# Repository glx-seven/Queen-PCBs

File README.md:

# Queen-PCBs
These are some Blinky-LED pendants I made a while ago. 

The main components are:
* BQ25570 energy harvesting controller
* KXOB25-05X3F mini solar cell
* MAL219691153E3 4F super-cap (probably has to be replaced with something else due to availability)
* PIC16LF18346-E/GZ (QFN20) MCU (if you're using 1.8V turn off the brown-out detection to make it run properly)

The programming pins match the PICKIT debugger, so you can stick some pogo-pins in the connector and hold it onto the pins to flash th firmware.
I did also upload the MPLAB-X project files for the firmware, it's not very good or complex tho, it just blinks some LEDs.

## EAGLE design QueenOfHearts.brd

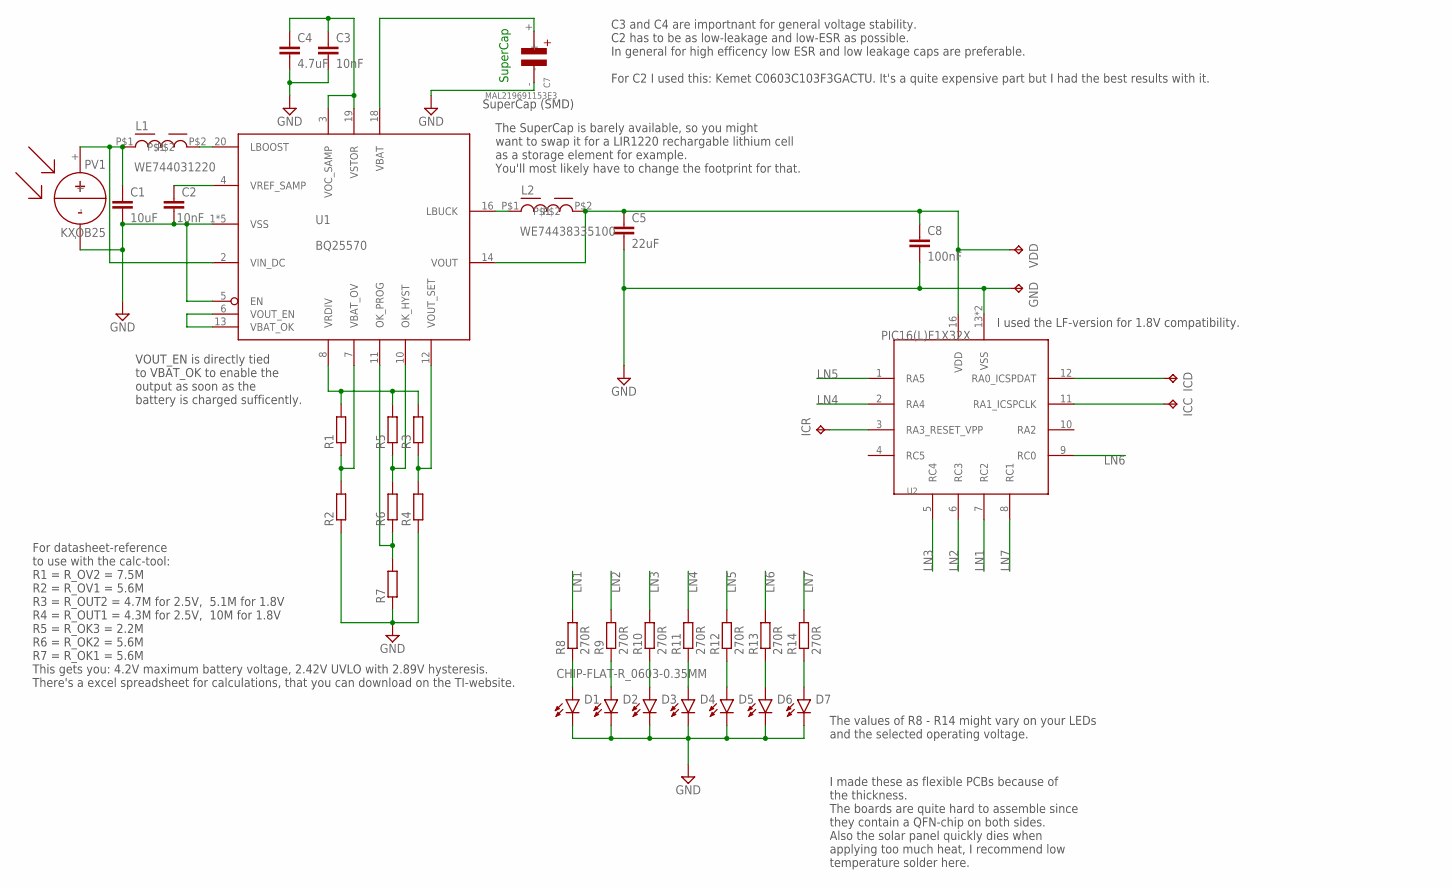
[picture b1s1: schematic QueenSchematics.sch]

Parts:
C1: 10uF; C0603K
C2, C3: 10nF; C0603K
C4: 4.7uF; C0603K
C5: 22uF; C0603K
C7: MAL219691153E3; MAL219691153E2
C8: 100nF; C0603K
D1, D2, D3, D4, D5, D6, D7: CHIP-FLAT-R_0603-0.35MM; LEDC1608X35N
GND: TPTP06SQ; TP06SQ
ICC: TPTP06SQ; TP06SQ
ICD: TPTP06SQ; TP06SQ
ICR: TPTP06SQ; TP06SQ
L1: WE744031220
L2: WE74438335100
PV1: KXOB25
R1, R2, R3, R4, R5, R6, R7: R-EU_R0603; R0603
R8, R9, R10, R11, R12, R13, R14: 270R; R0603
U1: BQ25570; QFN50P350X350X90-21T205N
U2: PIC16(L)F1X32X; QFN65P400X400X50-17T260N
VDD: TPTP06SQ; TP06SQ

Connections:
GND: C1.2, C2.2, C3.2, C4.2, C5.2, C7.-, C8.2, D1.C, D2.C, D3.C, D4.C, D5.C, D6.C, D7.C, GND.TP, PV1.-, R2.1, R4.1, R7.1, U1.1 (VSS), U1.5 (EN), U1.9 (VSS), U1.15 (VSS), U1.17 (VSS), U1.21 (VSS), U2.13 (VSS), U2.17 (VSS)
LN1: R8.2, U2.7 (RC2)
LN2: R9.2, U2.6 (RC3)
LN3: R10.2, U2.5 (RC4)
LN4: R11.2, U2.2 (RA4)
LN5: R12.2, U2.1 (RA5)
LN6: R13.2, U2.9 (RC0)
LN7: R14.2, U2.8 (RC1)
unnamed: L1.P$2, U1.20 (LBOOST)
unnamed: C1.1, L1.P$1, PV1.+, U1.2 (VIN_DC)
unnamed: C2.1, U1.4 (VREF_SAMP)
unnamed: L2.P$1, U1.16 (LBUCK)
unnamed: C3.1, C4.1, U1.3 (VOC_SAMP), U1.19 (VSTOR)
unnamed: U1.6 (VOUT_EN), U1.13 (VBAT_OK)
unnamed: C5.1, C8.1, L2.P$2, U1.14 (VOUT), U2.16 (VDD), VDD.TP
unnamed: C7.+, U1.18 (VBAT)
unnamed: R1.1, R2.2, U1.7 (VBAT_OV)
unnamed: R5.1, R6.2, U1.10 (OK_HYST)
unnamed: R3.1, R4.2, U1.12 (VOUT_SET)
unnamed: R6.1, R7.2, U1.11 (OK_PROG)
unnamed: ICR.TP, U2.3 (RA3_RESET_VPP)
unnamed: ICD.TP, U2.12 (RA0_ICSPDAT)
unnamed: ICC.TP, U2.11 (RA1_ICSPCLK)
unnamed: D1.A, R8.1
unnamed: D2.A, R9.1
unnamed: D3.A, R10.1
unnamed: D4.A, R11.1
unnamed: D5.A, R12.1
unnamed: D6.A, R13.1
unnamed: D7.A, R14.1
VRDRV: R1.2, R3.2, R5.2, U1.8 (VRDIV)

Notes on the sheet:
For datasheet-reference to use with the calc-tool: R1 = R_OV2 = 7.5M R2 = R_OV1 = 5.6M R3 = R_OUT2 = 4.7M for 2.5V, 5.1M for 1.8V R4 = R_OUT1 = 4.3M for 2.5V, 10M for 1.8V R5 = R_OK3 = 2.2M R6 = R_OK2 = 5.6M R7 = R_OK1 = 5.6M This gets you: 4.2V maximum battery voltage, 2.42V UVLO with 2.89V hyster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
SuperCap
SuperCap (SMD)
C3 and C4 are importnant for general voltage stability. C2 has to be as low-leakage and low-ESR as possible. In general for high efficency low ESR and low leakage caps are preferable. For C2 I used this: Kemet C0603C103F3GACTU. It's a quite expensive part but I had the best results with it.
VOUT_EN is directly tied to VBAT_OK to enable the output as soon as the battery is charged sufficently.
The SuperCap is barely available, so you might want to swap it for a LIR1220 rechargable lithium cell as a storage element for example. You'll most likely have to change the footprint for that.
I used the LF-version for 1.8V compatibility.
The values of R8 - R14 might vary on your LEDs and the selected operating voltage.
I made these as flexible PCBs because of the thickness. The boards are quite hard to assemble since they contain a QFN-chip on both sides. Also the solar panel quickly dies when applying too much heat, I recommend low temperature solder here.

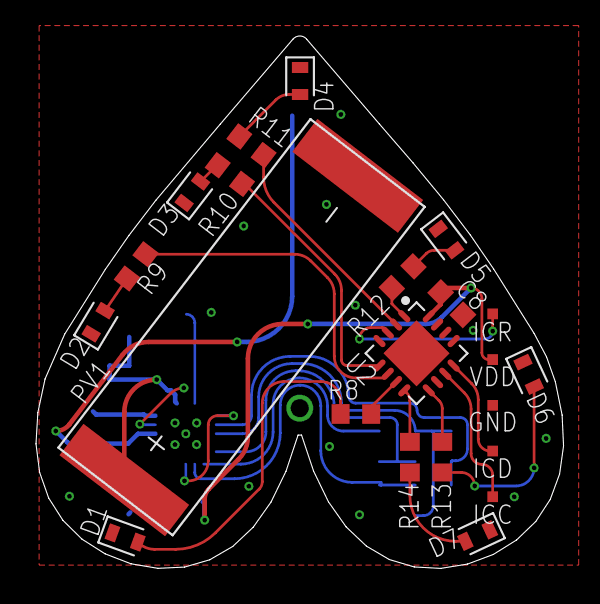
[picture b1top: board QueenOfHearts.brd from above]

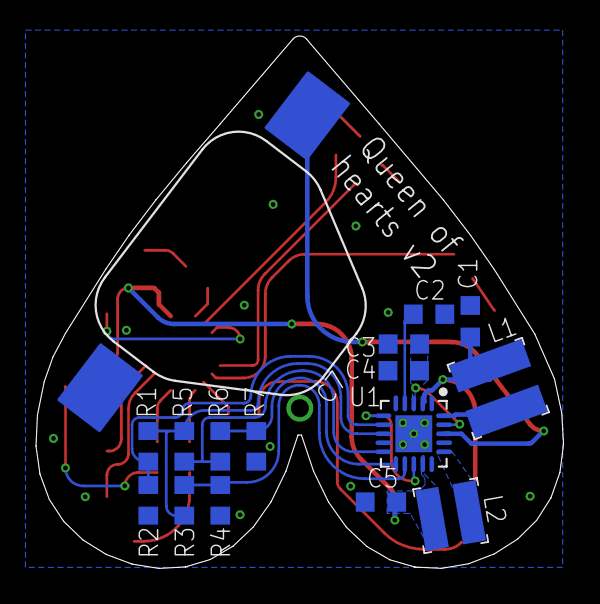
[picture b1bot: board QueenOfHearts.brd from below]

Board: 2 copper layers, 29.3 x 29.6 mm, 38 parts (16 on the bottom side), 31 nets.
